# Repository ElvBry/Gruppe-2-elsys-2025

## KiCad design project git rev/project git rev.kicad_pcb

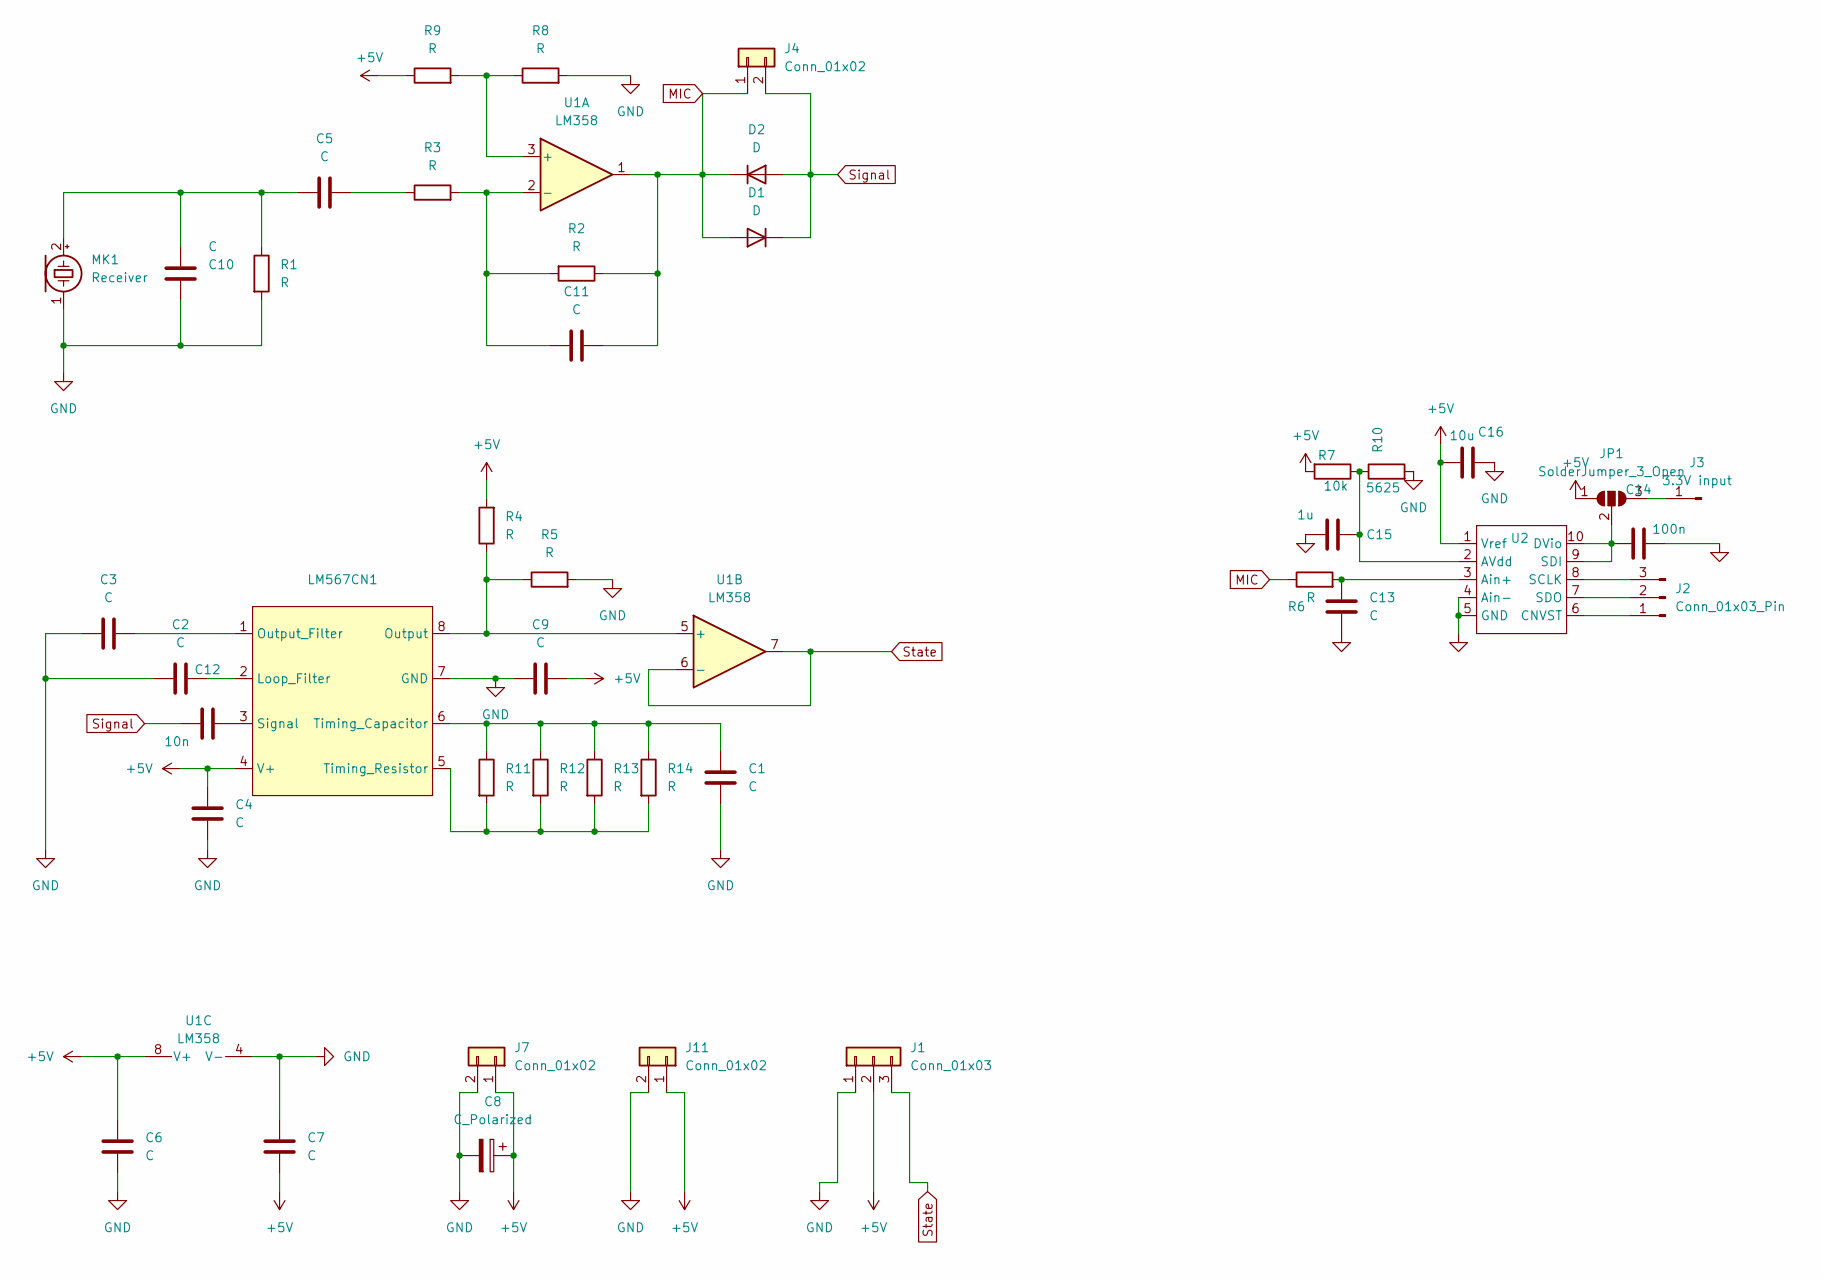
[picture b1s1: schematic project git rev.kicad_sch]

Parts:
C1, C2, C3, C4, C5, C6, C7, C9, C10, C11, C13: C; C_Rect_L4.6mm_W2.0mm_P2.50mm_MKS02_FKP02
C8: C_Polarized; CP_Radial_D5.0mm_P2.50mm
C12: 10n; C_Rect_L4.6mm_W2.0mm_P2.50mm_MKS02_FKP02
C14: 100n; C_Rect_L4.6mm_W2.0mm_P2.50mm_MKS02_FKP02
C15: 1u; C_Rect_L4.6mm_W2.0mm_P2.50mm_MKS02_FKP02
C16: 10u; C_Rect_L4.6mm_W2.0mm_P2.50mm_MKS02_FKP02
D1, D2: D; D_A-405_P7.62mm_Horizontal
J1: Conn_01x03; PinHeader_1x03_P2.54mm_Vertical
J2: Conn_01x03_Pin; PinHeader_1x03_P2.54mm_Vertical
J3: 3.3V input; PinHeader_1x01_P2.54mm_Vertical
J4, J7, J11: Conn_01x02; PinHeader_1x02_P2.54mm_Vertical
JP1: SolderJumper_3_Open; SolderJumper-3_P2.0mm_Open_TrianglePad1.0x1.5mm
LM567CN1: DIP-8_W10.16mm
MK1: Receiver; UR-1640K-TT-2-R
R1, R2, R3, R4, R5, R6, R8, R9, R11, R12, R13, R14: R; R_Axial_DIN0207_L6.3mm_D2.5mm_P10.16mm_Horizontal
R7: 10k; R_Axial_DIN0207_L6.3mm_D2.5mm_P10.16mm_Horizontal
R10: 5625; R_Axial_DIN0207_L6.3mm_D2.5mm_P10.16mm_Horizontal
U1: LM358; DIP-8_W10.16mm
U2: TDFN-10-1EP_2x3mm_P0.5mm_EP0.9x2mm

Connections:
+5V: C4.2, C6.1, C7.2, C8.1, C9.1, C16.1, J1.2, J7.1, J11.1, JP1.1 (A), LM567CN1.4 (V+), R4.2, R7.2, R9.1, U1.8 (V+), U2.1 (Vref)
GND: C1.2, C2.1, C3.1, C4.1, C6.2, C7.1, C8.2, C9.2, C10.1, C13.2, C14.2, C15.1, C16.2, J1.1, J7.2, J11.2, LM567CN1.7 (GND), MK1.1 (-), R1.2, R5.2, R8.2, R10.2, U1.4 (V-), U2.4 (Ain-), U2.5 (GND)
MIC: C11.2, D1.2 (A), D2.1 (K), J4.1, R2.1, R6.1, U1.1
unnamed: C5.2, R3.1
unnamed: J2.1, U2.6 (CNVST)
unnamed: J2.2, U2.7 (SDO)
unnamed: J2.3, U2.8 (SCLK)
unnamed: J3.1, JP1.3 (B)
unnamed: C14.1, JP1.2 (C), U2.9 (SDI), U2.10 (DVio)
unnamed: C2.2, LM567CN1.2 (Loop_Filter)
unnamed: LM567CN1.8 (Output), R4.1, R5.1, U1.5 (+)
unnamed: C3.2, LM567CN1.1 (Output_Filter)
unnamed: C12.2, LM567CN1.3 (Signal)
unnamed: C1.1, LM567CN1.6 (Timing_Capacitor), R11.1, R12.1, R13.1, R14.1
unnamed: LM567CN1.5 (Timing_Resistor), R11.2, R12.2, R13.2, R14.2
unnamed: C5.1, C10.2, MK1.2 (+), R1.1
unnamed: R8.1, R9.2, U1.3 (+)
unnamed: C11.1, R2.2, R3.2, U1.2 (-)
unnamed: C15.2, R7.1, R10.1, U2.2 (AVdd)
unnamed: C13.1, R6.2, U2.3 (Ain+)
Signal: C12.1, D1.1 (K), D2.2 (A), J4.2
State: J1.3, U1.6 (-), U1.7

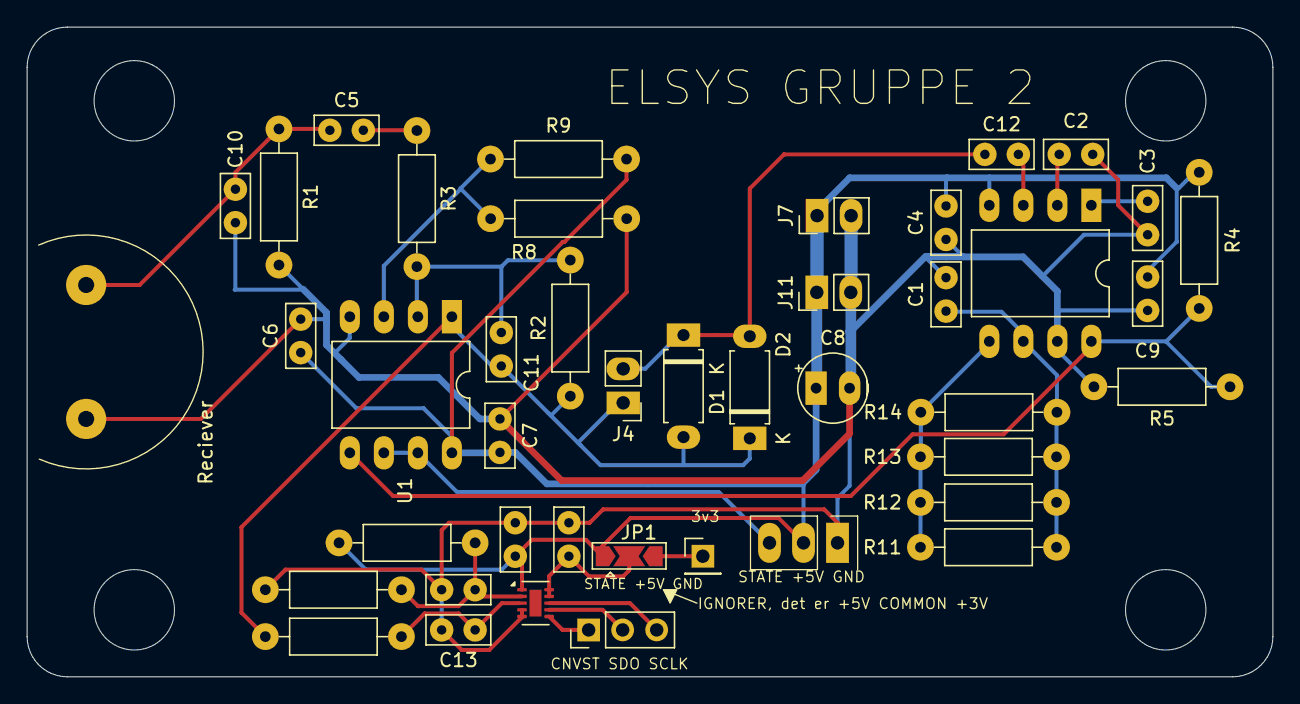
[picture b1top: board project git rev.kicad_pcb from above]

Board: 2 copper layers, 93.0 x 48.5 mm, 43 parts (0 on the bottom side), 22 nets.

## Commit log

2025-02-13 Lagt til python simulering i 3D med simulert støy
2025-02-17 ESP32DSPkode.ino
    stable and working
2025-02-17 Create ESP32_DUMMY_TRANSMITTER.ino
    working dummy transmitter
2025-02-17 Rename ESP32DSPkode.ino to ESP32_DSP.ino
2025-03-04 Noen estetiske endringer + satt kanten og hull til milimeter grid
2025-03-06 Endret rutinger slik at referansepunkt ble like for deler av elektronikken (GND/5V) Endret unødvendig tykke ruter til tynne Endret rutene mellom de to strømtilkoblingene til å være 1 mm tykke Formink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
2025-03-10 La til MCP adcen i kretsen og bestilte 👍
2025-03-11 Create gammelDSPcodeESP-IDF
2025-03-12 Create ESP-IDF_SPI_SLAVE_TEST
2025-03-18 La til krets PDF
2025-03-24 Create ESP32_DUMMY_TRANSMITTER_TOUCH
2025-03-24 Rename ESP32_DUMMY_TRANSMITTER_TOUCH to ESP32_DUMMY_TRANSMITTER_TOUCH.ino
2025-03-24 Update and rename gammelDSPcodeESP-IDF to FPGAtilESP-DSPcode-IDF
2025-03-24 Rename FPGAtilESP-DSPcode-IDF to FPGAtilESP-DSPcode-IDF.c
2025-03-25 Update FPGAtilESP-DSPcode-IDF.c
    Fungerende versjon uten automatisk kalibrering
2025-03-27 Create ThresholdMonteCarlo.cpp
    Fungerende monte carlo simulasjon av signaldeteksjon i siste bøtte
2025-03-27 Update ThresholdMonteCarlo.cpp
    Fungerende versjon
2025-03-28 Create ESP_kode_folder
2025-03-28 Update and rename ESP_kode_folder to ESP32/ESP-DSP-FPGA-NY
2025-03-28 Update and rename ESP-IDF_SPI_SLAVE_TEST to ESP32/SPI_SLAVE_TEST
2025-03-28 Rename ESP32_DSP.ino to ArduinoESP32/ESP32_DSP.ino
2025-03-28 Rename ESP32_DUMMY_TRANSMITTER.ino to ArduinoESP32/DUMMY_TRANSMITTER.ino
2025-03-28 Rename ESP-DSP-FPGA-NY to DSP_FPGA_NEW
2025-03-28 Rename DSP_FPGA_NEW to ESP_DSP_NEW
2025-03-28 Rename SPI_SLAVE_TEST to SPI_SLAVE_TEST
2025-03-28 Rename ESP32_DUMMY_TRANSMITTER_TOUCH.ino to ArduinoESP32/ESP32_DUMMY_TRANSMITTER_TOUCH.ino
2025-03-28 Rename FPGAtilESP-DSPcode-IDF.c to ESP-IDF/ESP_DSP_old.c
2025-03-28 Rename ESP_DSP_NEW to ESP_DSP_new.c
2025-03-28 Rename monteCarloDSP.cpp to testPrograms/monteCarloDSP.cpp
2025-03-28 Rename plotFraSerial3D.py to testPrograms/plotFraSerial3D.py
2025-03-28 Rename pythonPlotThreshold.py to testPrograms/pythonPlotThreshold.py
2025-03-28 Rename pythonPlotThreshold.py to plotThreshold.py
2025-03-28 Rename timedelayCalculator.py to testPrograms/timedelayCalculator.py
2025-03-28 Rename pythonTDOA.py to testPrograms/pythonTDOA.py
2025-03-28 Rename pythonTDOA.py to TDOAtest.py
2025-03-28 Create align_buffers_old_approach
2025-03-28 Rename align_buffers_old_approach to align_buffers_old_approach.c
2025-04-02 Update ESP_DSP_new.c
    Fungerende versjon med simulert data fra FPGA. Trenger forbedring for å unngå høyt antall falsk positive målinger
2025-05-04 Update monteCarloDSP.cpp
    FinalTest
2025-05-04 Rename FPGA_SPI_temp.ice to FPGA_SPI.ice
